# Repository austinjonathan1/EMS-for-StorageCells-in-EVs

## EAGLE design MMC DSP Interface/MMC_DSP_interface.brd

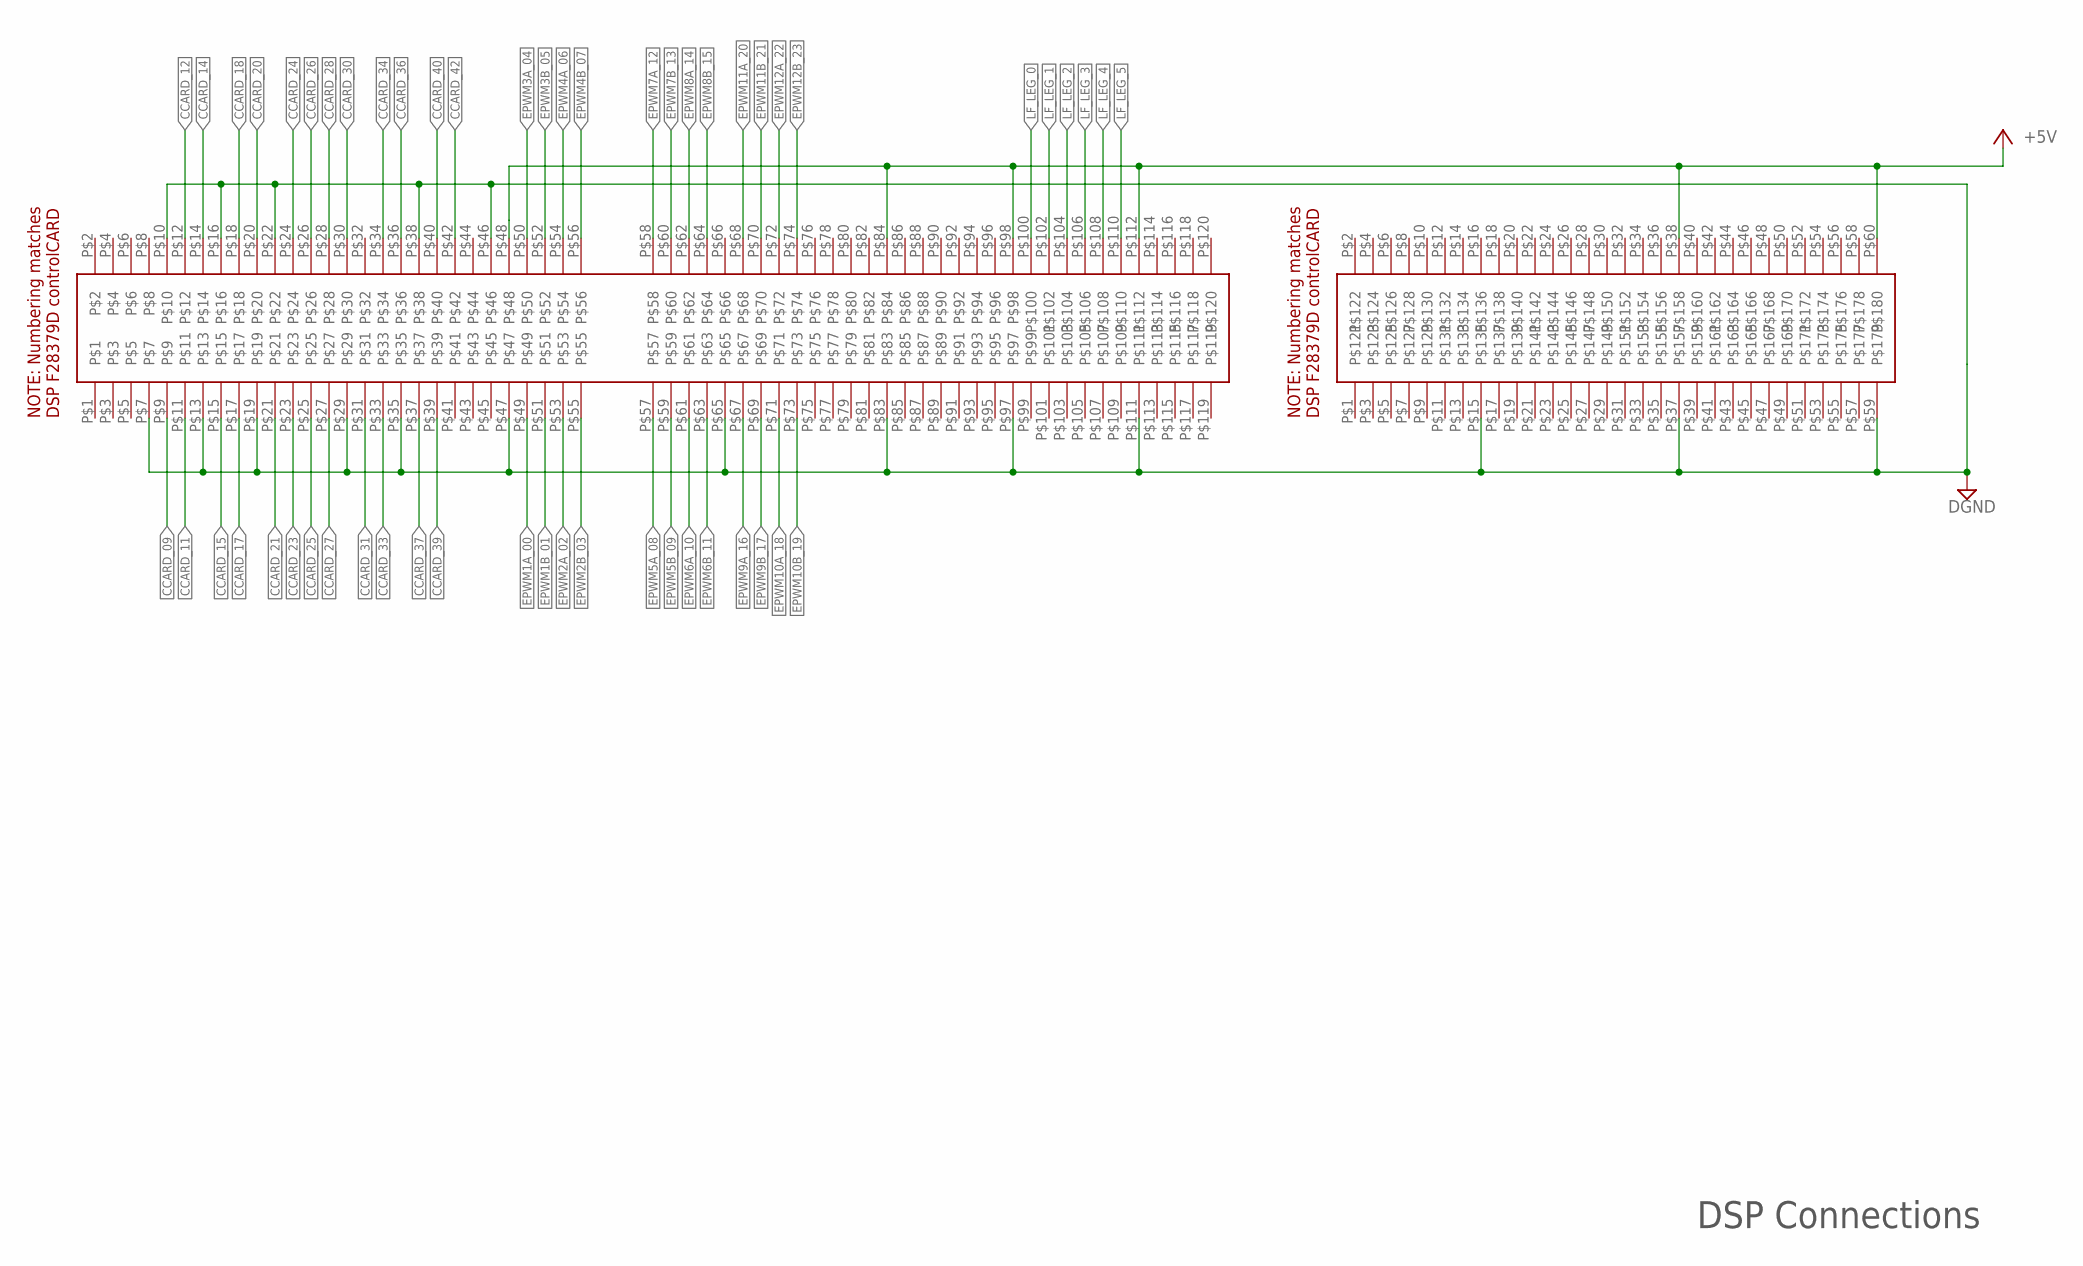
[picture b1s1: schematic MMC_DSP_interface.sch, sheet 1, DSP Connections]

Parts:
U$1: HSEC8-160-01-L-DV-A-BL
U$2: HSEC8-130-01-SM-DV-A

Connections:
+5V: U$1.P$48, U$1.P$84, U$1.P$98, U$1.P$112, U$2.P$38, U$2.P$60; also elsewhere on the board
CCARD_09: U$1.P$9; also elsewhere on the board
CCARD_11: U$1.P$11; also elsewhere on the board
CCARD_12: U$1.P$12; also elsewhere on the board
CCARD_14: U$1.P$14; also elsewhere on the board
CCARD_15: U$1.P$15; also elsewhere on the board
CCARD_17: U$1.P$17; also elsewhere on the board
CCARD_18: U$1.P$18; also elsewhere on the board
CCARD_20: U$1.P$20; also elsewhere on the board
CCARD_21: U$1.P$21; also elsewhere on the board
CCARD_23: U$1.P$23; also elsewhere on the board
CCARD_24: U$1.P$24; also elsewhere on the board
CCARD_25: U$1.P$25; also elsewhere on the board
CCARD_26: U$1.P$26; also elsewhere on the board
CCARD_27: U$1.P$27; also elsewhere on the board
CCARD_28: U$1.P$28; also elsewhere on the board
CCARD_30: U$1.P$30; also elsewhere on the board
CCARD_31: U$1.P$31; also elsewhere on the board
CCARD_33: U$1.P$33; also elsewhere on the board
CCARD_34: U$1.P$34; also elsewhere on the board
CCARD_36: U$1.P$36; also elsewhere on the board
CCARD_37: U$1.P$37; also elsewhere on the board
CCARD_39: U$1.P$39; also elsewhere on the board
CCARD_40: U$1.P$40; also elsewhere on the board
CCARD_42: U$1.P$42; also elsewhere on the board
DGND: U$1.P$7, U$1.P$10, U$1.P$13, U$1.P$16, U$1.P$19, U$1.P$22, U$1.P$29, U$1.P$35, U$1.P$38, U$1.P$46, U$1.P$47, U$1.P$65, U$1.P$83, U$1.P$97, U$1.P$111, U$2.P$15, U$2.P$37, U$2.P$59; also elsewhere on the board
EPWM1A_00: U$1.P$49; also elsewhere on the board
EPWM1B_01: U$1.P$51; also elsewhere on the board
EPWM2A_02: U$1.P$53; also elsewhere on the board
EPWM2B_03: U$1.P$55; also elsewhere on the board
EPWM3A_04: U$1.P$50; also elsewhere on the board
EPWM3B_05: U$1.P$52; also elsewhere on the board
EPWM4A_06: U$1.P$54; also elsewhere on the board
EPWM4B_07: U$1.P$56; also elsewhere on the board
EPWM5A_08: U$1.P$57; also elsewhere on the board
EPWM5B_09: U$1.P$59; also elsewhere on the board
EPWM6A_10: U$1.P$61; also elsewhere on the board
EPWM6B_11: U$1.P$63; also elsewhere on the board
EPWM7A_12: U$1.P$58; also elsewhere on the board
EPWM7B_13: U$1.P$60; also elsewhere on the board
EPWM8A_14: U$1.P$62; also elsewhere on the board
EPWM8B_15: U$1.P$64; also elsewhere on the board
EPWM9A_16: U$1.P$67; also elsewhere on the board
EPWM9B_17: U$1.P$69; also elsewhere on the board
EPWM10A_18: U$1.P$71; also elsewhere on the board
EPWM10B_19: U$1.P$73; also elsewhere on the board
EPWM11A_20: U$1.P$68; also elsewhere on the board
EPWM11B_21: U$1.P$70; also elsewhere on the board
EPWM12A_22: U$1.P$72; also elsewhere on the board
EPWM12B_23: U$1.P$74; also elsewhere on the board
LF_LEG_0: U$1.P$100; also elsewhere on the board
LF_LEG_1: U$1.P$102; also elsewhere on the board
LF_LEG_2: U$1.P$104; also elsewhere on the board
LF_LEG_3: U$1.P$106; also elsewhere on the board
LF_LEG_4: U$1.P$108; also elsewhere on the board
LF_LEG_5: U$1.P$110; also elsewhere on the board

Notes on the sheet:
DSP Connections

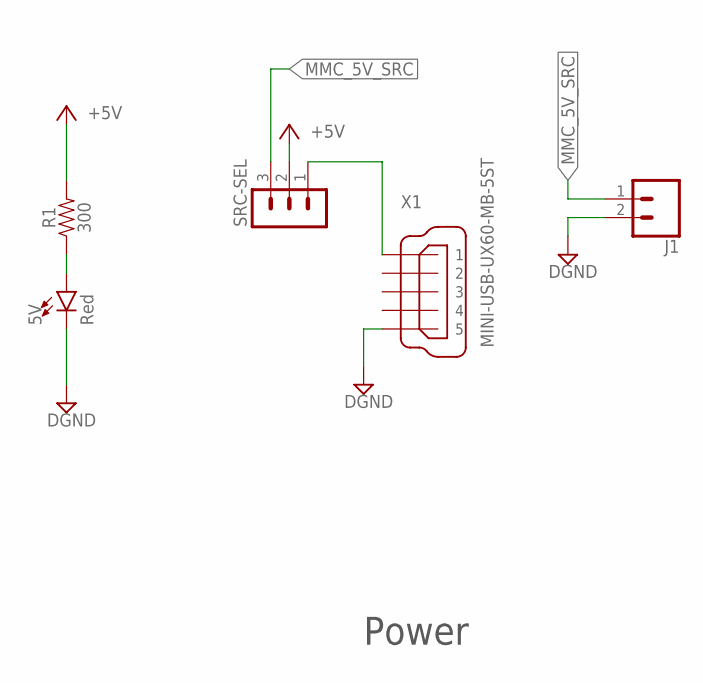
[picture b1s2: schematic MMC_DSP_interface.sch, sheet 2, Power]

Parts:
5V: Red; LED-0603
J1: CONN_02; 1X02
R1: 300; 0603
SRC-SEL: MA03-1
X1: MINI-USB-UX60-MB-5ST; UX60-MB-5ST

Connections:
+5V: R1.2, SRC-SEL.2; also elsewhere on the board
DGND: 5V.C, J1.2, X1.5; also elsewhere on the board
MMC_5V_SRC: J1.1, SRC-SEL.3
unnamed: SRC-SEL.1, X1.1
unnamed: 5V.A, R1.1

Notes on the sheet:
Power

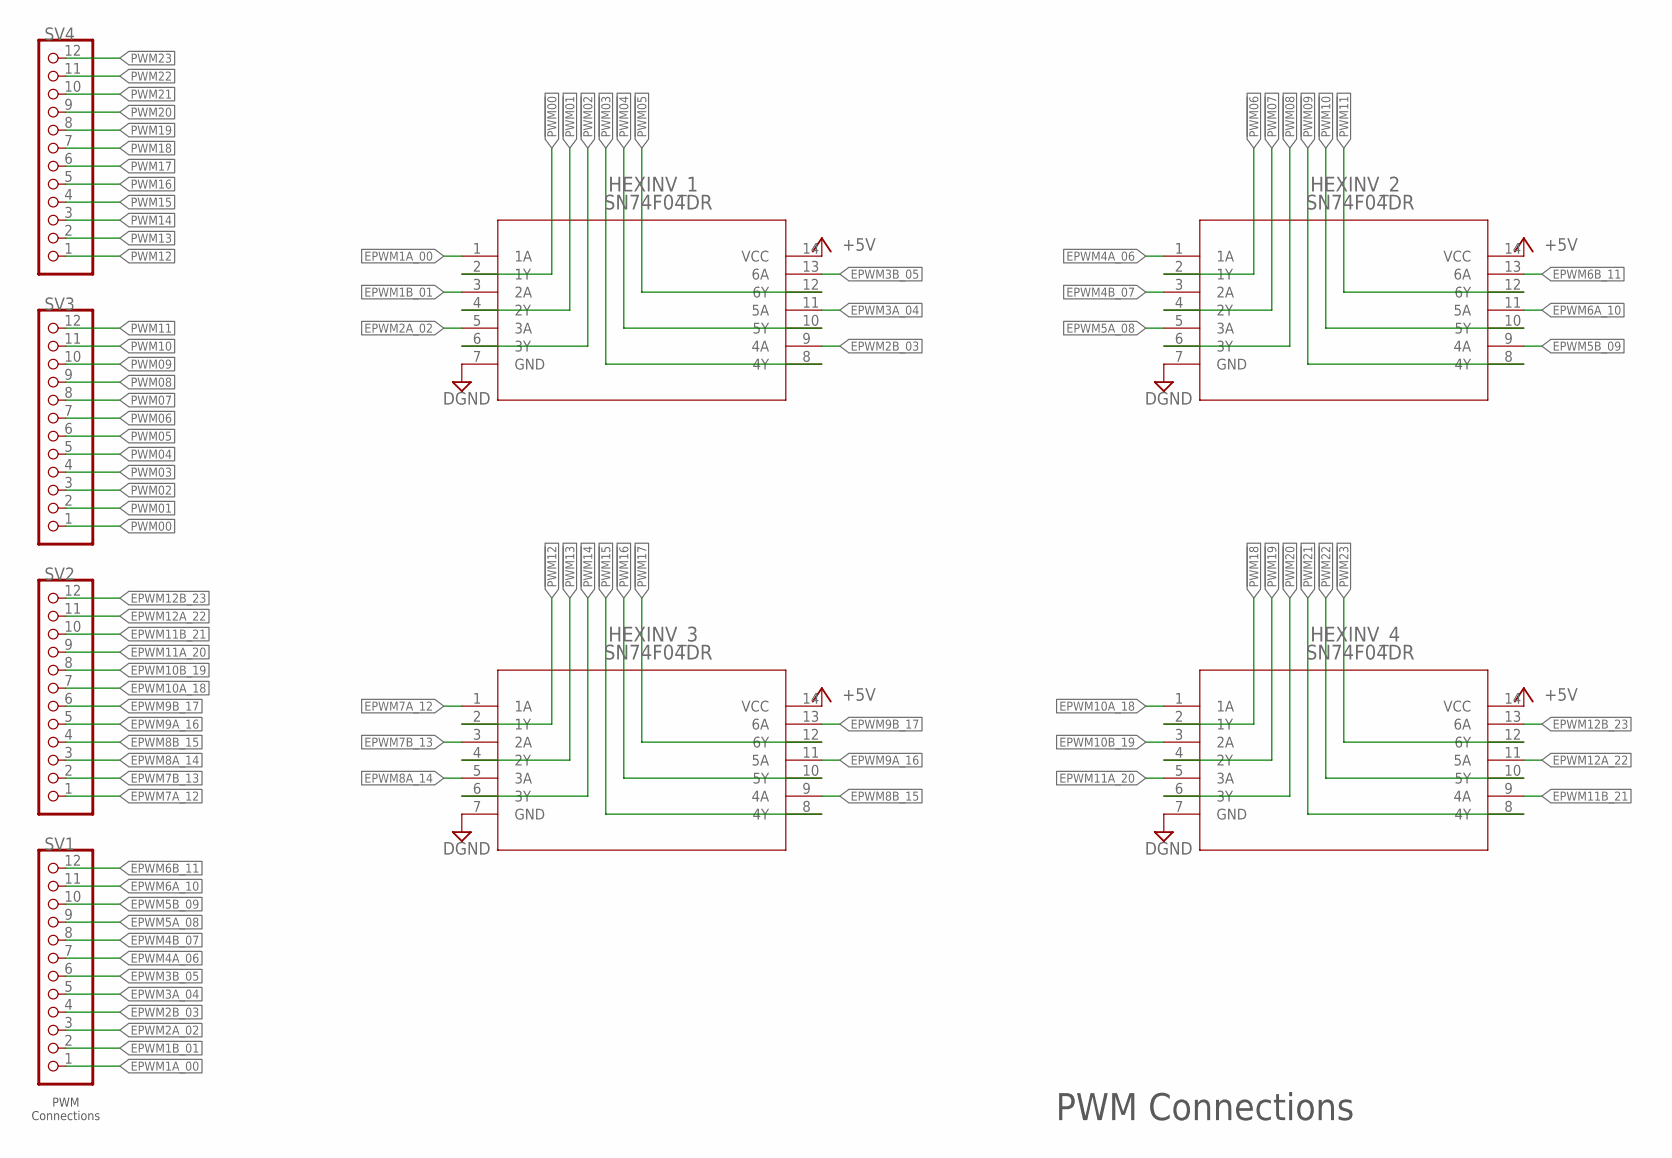
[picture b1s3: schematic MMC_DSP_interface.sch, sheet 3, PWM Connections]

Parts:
HEXINV_1, HEXINV_2, HEXINV_3, HEXINV_4: SN74F04DR; D14
SV1, SV2, SV3, SV4: PINHD-1X12-CB; 1X12-CB

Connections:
!PWM00: HEXINV_1.2 (1Y), SV3.1
!PWM01: HEXINV_1.4 (2Y), SV3.2
!PWM02: HEXINV_1.6 (3Y), SV3.3
!PWM03: HEXINV_1.8 (4Y), SV3.4
!PWM04: HEXINV_1.10 (5Y), SV3.5
!PWM05: HEXINV_1.12 (6Y), SV3.6
!PWM06: HEXINV_2.2 (1Y), SV3.7
!PWM07: HEXINV_2.4 (2Y), SV3.8
!PWM08: HEXINV_2.6 (3Y), SV3.9
!PWM09: HEXINV_2.8 (4Y), SV3.10
!PWM10: HEXINV_2.10 (5Y), SV3.11
!PWM11: HEXINV_2.12 (6Y), SV3.12
!PWM12: HEXINV_3.2 (1Y), SV4.1
!PWM13: HEXINV_3.4 (2Y), SV4.2
!PWM14: HEXINV_3.6 (3Y), SV4.3
!PWM15: HEXINV_3.8 (4Y), SV4.4
!PWM16: HEXINV_3.10 (5Y), SV4.5
!PWM17: HEXINV_3.12 (6Y), SV4.6
!PWM18: HEXINV_4.2 (1Y), SV4.7
!PWM19: HEXINV_4.4 (2Y), SV4.8
!PWM20: HEXINV_4.6 (3Y), SV4.9
!PWM21: HEXINV_4.8 (4Y), SV4.10
!PWM22: HEXINV_4.10 (5Y), SV4.11
!PWM23: HEXINV_4.12 (6Y), SV4.12
+5V: HEXINV_1.14 (VCC), HEXINV_2.14 (VCC), HEXINV_3.14 (VCC), HEXINV_4.14 (VCC); also elsewhere on the board
DGND: HEXINV_1.7 (GND), HEXINV_2.7 (GND), HEXINV_3.7 (GND), HEXINV_4.7 (GND); also elsewhere on the board
EPWM1A_00: HEXINV_1.1 (1A), SV1.1; also elsewhere on the board
EPWM1B_01: HEXINV_1.3 (2A), SV1.2; also elsewhere on the board
EPWM2A_02: HEXINV_1.5 (3A), SV1.3; also elsewhere on the board
EPWM2B_03: HEXINV_1.9 (4A), SV1.4; also elsewhere on the board
EPWM3A_04: HEXINV_1.11 (5A), SV1.5; also elsewhere on the board
EPWM3B_05: HEXINV_1.13 (6A), SV1.6; also elsewhere on the board
EPWM4A_06: HEXINV_2.1 (1A), SV1.7; also elsewhere on the board
EPWM4B_07: HEXINV_2.3 (2A), SV1.8; also elsewhere on the board
EPWM5A_08: HEXINV_2.5 (3A), SV1.9; also elsewhere on the board
EPWM5B_09: HEXINV_2.9 (4A), SV1.10; also elsewhere on the board
EPWM6A_10: HEXINV_2.11 (5A), SV1.11; also elsewhere on the board
EPWM6B_11: HEXINV_2.13 (6A), SV1.12; also elsewhere on the board
EPWM7A_12: HEXINV_3.1 (1A), SV2.1; also elsewhere on the board
EPWM7B_13: HEXINV_3.3 (2A), SV2.2; also elsewhere on the board
EPWM8A_14: HEXINV_3.5 (3A), SV2.3; also elsewhere on the board
EPWM8B_15: HEXINV_3.9 (4A), SV2.4; also elsewhere on the board
EPWM9A_16: HEXINV_3.11 (5A), SV2.5; also elsewhere on the board
EPWM9B_17: HEXINV_3.13 (6A), SV2.6; also elsewhere on the board
EPWM10A_18: HEXINV_4.1 (1A), SV2.7; also elsewhere on the board
EPWM10B_19: HEXINV_4.3 (2A), SV2.8; also elsewhere on the board
EPWM11A_20: HEXINV_4.5 (3A), SV2.9; also elsewhere on the board
EPWM11B_21: HEXINV_4.9 (4A), SV2.10; also elsewhere on the board
EPWM12A_22: HEXINV_4.11 (5A), SV2.11; also elsewhere on the board
EPWM12B_23: HEXINV_4.13 (6A), SV2.12; also elsewhere on the board

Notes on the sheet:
PWM Connections
PWM Connections

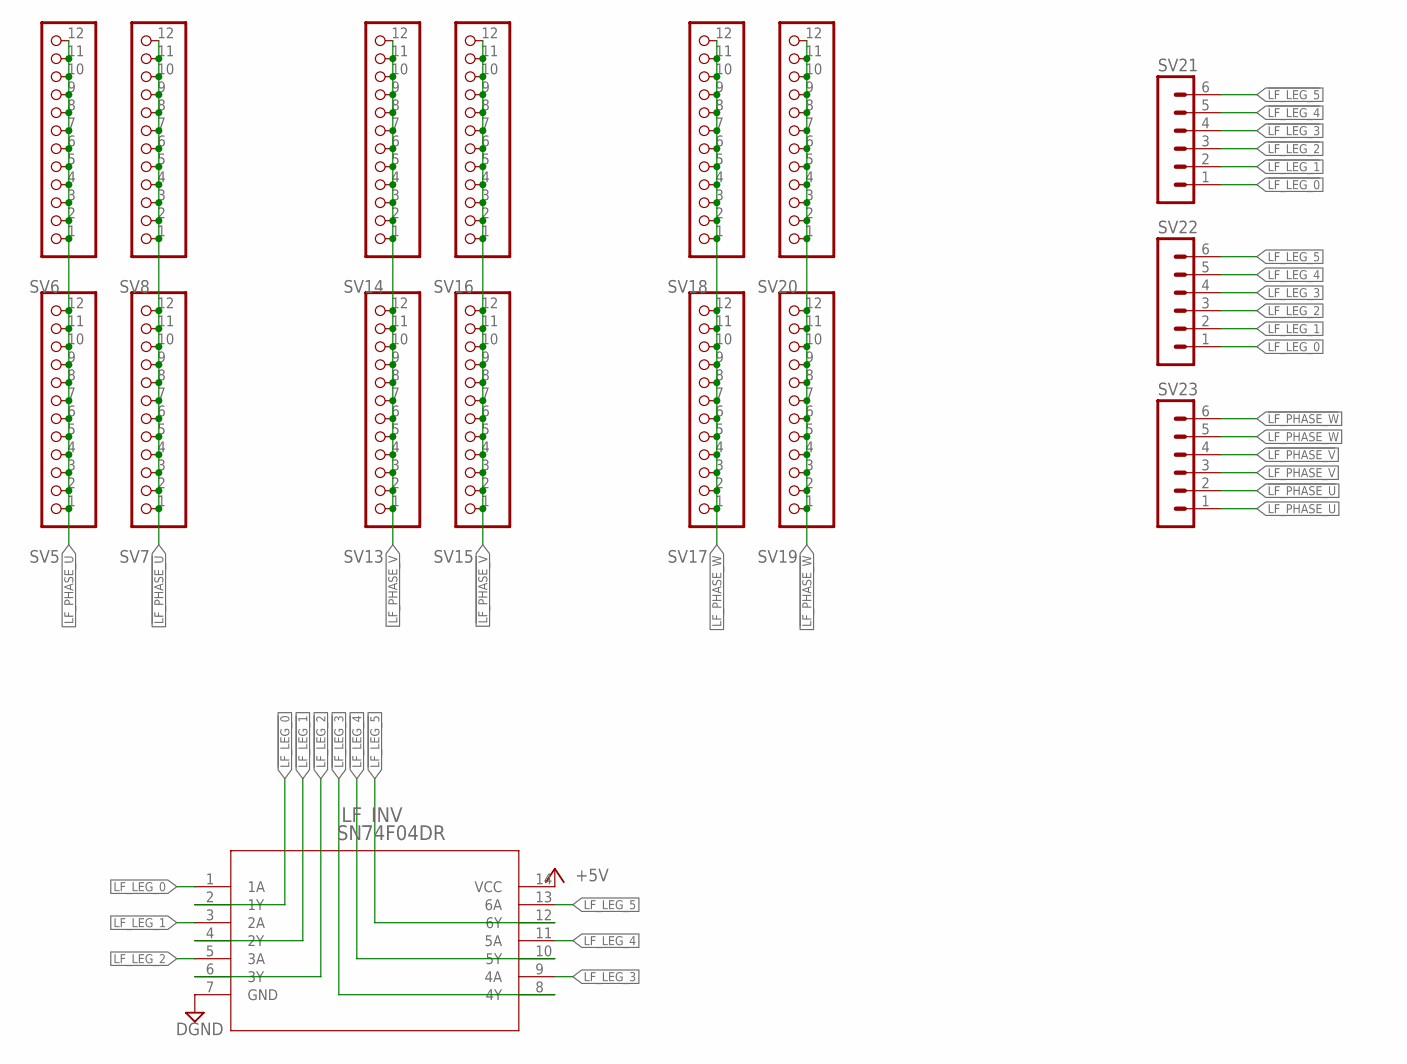
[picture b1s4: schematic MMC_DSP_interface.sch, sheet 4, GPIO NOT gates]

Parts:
LF_INV: SN74F04DR; D14
SV5, SV6, SV7, SV8, SV13, SV14, SV15, SV16, SV17, SV18, SV19, SV20: PINHD-1X12-CB; 1X12-CB
SV21, SV22, SV23: MA06-1

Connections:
!LF_LEG_0: LF_INV.2 (1Y), SV21.1
!LF_LEG_1: LF_INV.4 (2Y), SV21.2
!LF_LEG_2: LF_INV.6 (3Y), SV21.3
!LF_LEG_3: LF_INV.8 (4Y), SV21.4
!LF_LEG_4: LF_INV.10 (5Y), SV21.5
!LF_LEG_5: LF_INV.12 (6Y), SV21.6
!LF_PHASE_U: SV7.1, SV7.2, SV7.3, SV7.4, SV7.5, SV7.6, SV7.7, SV7.8, SV7.9, SV7.10, SV7.11, SV7.12, SV8.1, SV8.2, SV8.3, SV8.4, SV8.5, SV8.6, SV8.7, SV8.8, SV8.9, SV8.10, SV8.11, SV8.12, SV23.2
!LF_PHASE_V: SV15.1, SV15.2, SV15.3, SV15.4, SV15.5, SV15.6, SV15.7, SV15.8, SV15.9, SV15.10, SV15.11, SV15.12, SV16.1, SV16.2, SV16.3, SV16.4, SV16.5, SV16.6, SV16.7, SV16.8, SV16.9, SV16.10, SV16.11, SV16.12, SV23.4
!LF_PHASE_W: SV19.1, SV19.2, SV19.3, SV19.4, SV19.5, SV19.6, SV19.7, SV19.8, SV19.9, SV19.10, SV19.11, SV19.12, SV20.1, SV20.2, SV20.3, SV20.4, SV20.5, SV20.6, SV20.7, SV20.8, SV20.9, SV20.10, SV20.11, SV20.12, SV23.6
+5V: LF_INV.14 (VCC); also elsewhere on the board
DGND: LF_INV.7 (GND); also elsewhere on the board
LF_LEG_0: LF_INV.1 (1A), SV22.1; also elsewhere on the board
LF_LEG_1: LF_INV.3 (2A), SV22.2; also elsewhere on the board
LF_LEG_2: LF_INV.5 (3A), SV22.3; also elsewhere on the board
LF_LEG_3: LF_INV.9 (4A), SV22.4; also elsewhere on the board
LF_LEG_4: LF_INV.11 (5A), SV22.5; also elsewhere on the board
LF_LEG_5: LF_INV.13 (6A), SV22.6; also elsewhere on the board
LF_PHASE_U: SV5.1, SV5.2, SV5.3, SV5.4, SV5.5, SV5.6, SV5.7, SV5.8, SV5.9, SV5.10, SV5.11, SV5.12, SV6.1, SV6.2, SV6.3, SV6.4, SV6.5, SV6.6, SV6.7, SV6.8, SV6.9, SV6.10, SV6.11, SV6.12, SV23.1
LF_PHASE_V: SV13.1, SV13.2, SV13.3, SV13.4, SV13.5, SV13.6, SV13.7, SV13.8, SV13.9, SV13.10, SV13.11, SV13.12, SV14.1, SV14.2, SV14.3, SV14.4, SV14.5, SV14.6, SV14.7, SV14.8, SV14.9, SV14.10, SV14.11, SV14.12, SV23.3
LF_PHASE_W: SV17.1, SV17.2, SV17.3, SV17.4, SV17.5, SV17.6, SV17.7, SV17.8, SV17.9, SV17.10, SV17.11, SV17.12, SV18.1, SV18.2, SV18.3, SV18.4, SV18.5, SV18.6, SV18.7, SV18.8, SV18.9, SV18.10, SV18.11, SV18.12, SV23.5

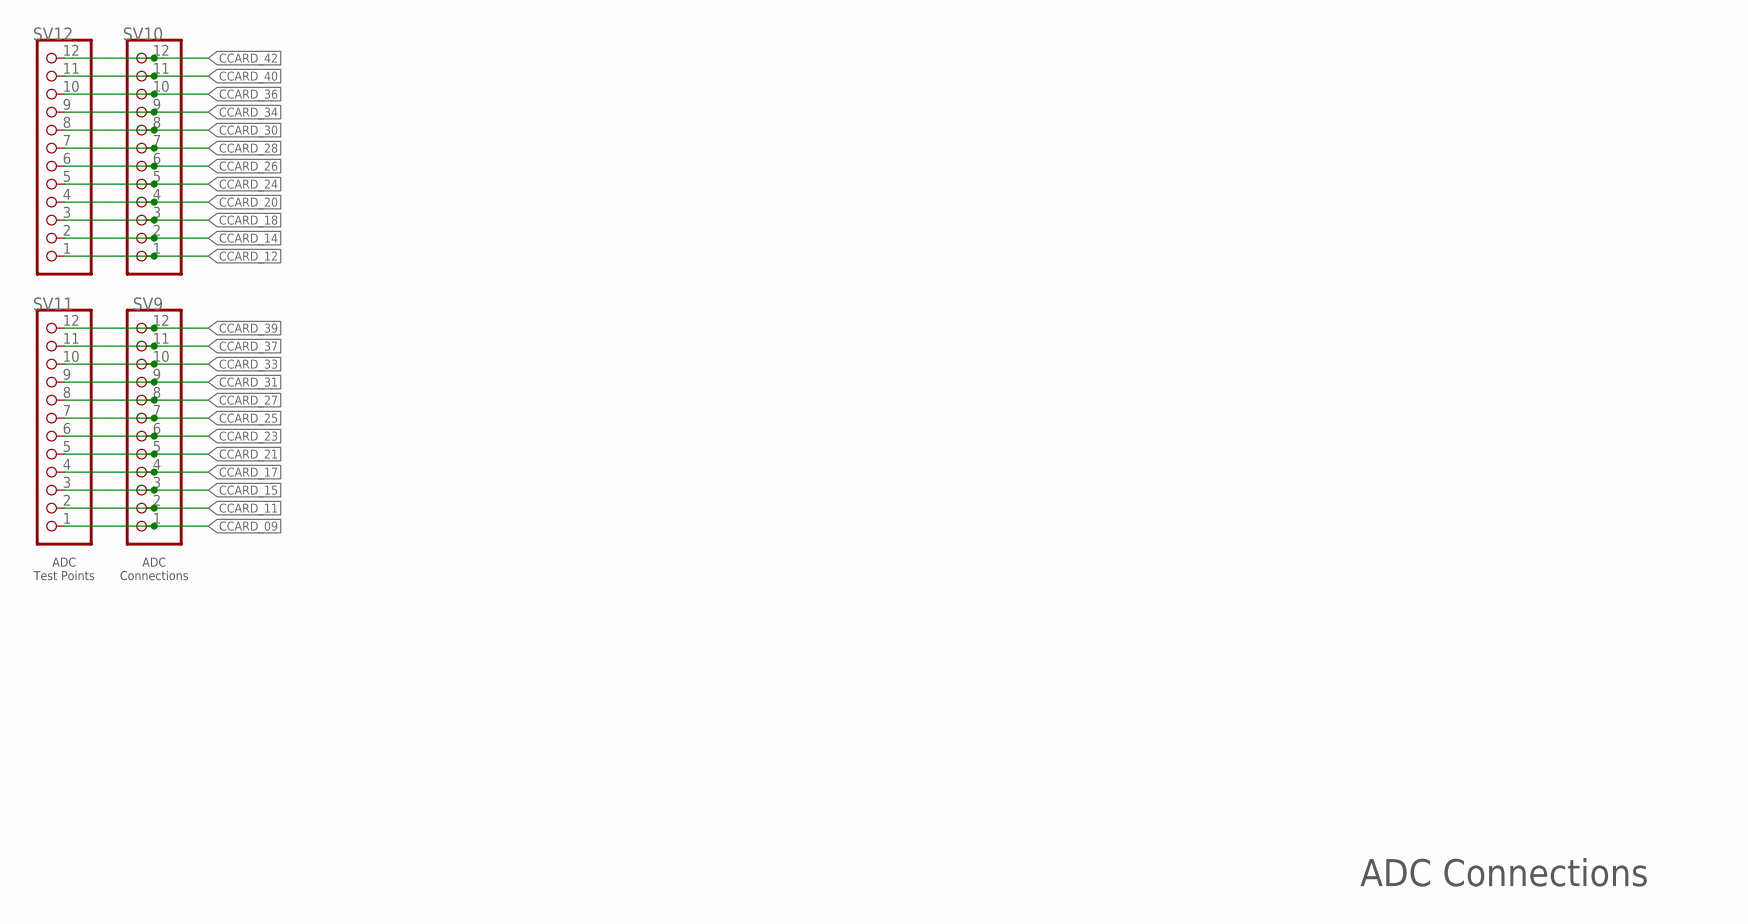
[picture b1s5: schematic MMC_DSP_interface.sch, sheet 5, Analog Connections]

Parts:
SV9, SV10, SV11, SV12: PINHD-1X12-CB; 1X12-CB

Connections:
CCARD_09: SV9.1, SV11.1; also elsewhere on the board
CCARD_11: SV9.2, SV11.2; also elsewhere on the board
CCARD_12: SV10.1, SV12.1; also elsewhere on the board
CCARD_14: SV10.2, SV12.2; also elsewhere on the board
CCARD_15: SV9.3, SV11.3; also elsewhere on the board
CCARD_17: SV9.4, SV11.4; also elsewhere on the board
CCARD_18: SV10.3, SV12.3; also elsewhere on the board
CCARD_20: SV10.4, SV12.4; also elsewhere on the board
CCARD_21: SV9.5, SV11.5; also elsewhere on the board
CCARD_23: SV9.6, SV11.6; also elsewhere on the board
CCARD_24: SV10.5, SV12.5; also elsewhere on the board
CCARD_25: SV9.7, SV11.7; also elsewhere on the board
CCARD_26: SV10.6, SV12.6; also elsewhere on the board
CCARD_27: SV9.8, SV11.8; also elsewhere on the board
CCARD_28: SV10.7, SV12.7; also elsewhere on the board
CCARD_30: SV10.8, SV12.8; also elsewhere on the board
CCARD_31: SV9.9, SV11.9; also elsewhere on the board
CCARD_33: SV9.10, SV11.10; also elsewhere on the board
CCARD_34: SV10.9, SV12.9; also elsewhere on the board
CCARD_36: SV10.10, SV12.10; also elsewhere on the board
CCARD_37: SV9.11, SV11.11; also elsewhere on the board
CCARD_39: SV9.12, SV11.12; also elsewhere on the board
CCARD_40: SV10.11, SV12.11; also elsewhere on the board
CCARD_42: SV10.12, SV12.12; also elsewhere on the board

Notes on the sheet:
ADC Connections
ADC Connections
ADC Test Points

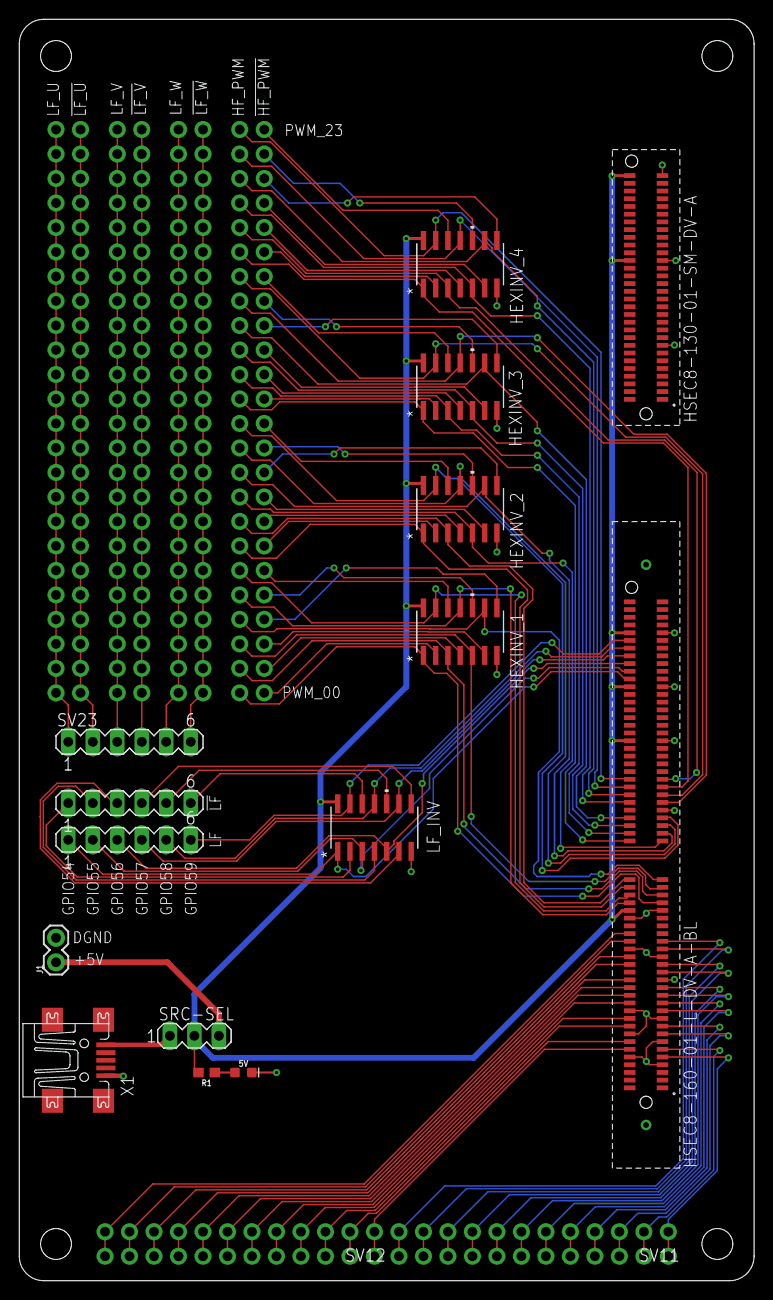
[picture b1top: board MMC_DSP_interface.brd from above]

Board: 2 copper layers, 76.2 x 130.8 mm, 35 parts (0 on the bottom side), 95 nets.

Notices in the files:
parts and their libraries:
SparkFun-LED: Licensing: Creative Commons ShareAlike 4.0 International - https://creativecommons.org/licenses/by-sa/4.0
